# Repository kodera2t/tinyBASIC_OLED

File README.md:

# TinyBasicPlus_OLED_support
	! PLEASE select LCD version if you are searching character LCD support for TinyBasicPlus!!, If you need graphic LCD support for TinyBasicPluse, please select OLED version. !
	SSD1306 compatible OLED/LCD (128x64 dots) support is added to TinyBasicPlus, using Adafruit_GFX lib. 
	Frame buffer for 21x8 characters is added for text display. Along this support, TVout and PS2 keyboard support is subtracted, assuming re-programmed Xbox360 or serial console usage for input device. (you can add PS/2, if you need) I refered the source code by Ben Heck's Retro Basic Computer. GRAPHIC related BASIC commands (currently supporting only direct command):  CLS (clear screen), LINE x0,y0,x1,y1 CIRCLE x,y,radius FILLCIRCLE x,y,radius ROUNDRECT x,y,w,h,r FILLROUNDRECT x,y,w,h,r are added just for graphic test..
	Not only Arduino sketch, also circuit schematic and circuit pattern (.brd) is uploaded for your quick test of OLED version.

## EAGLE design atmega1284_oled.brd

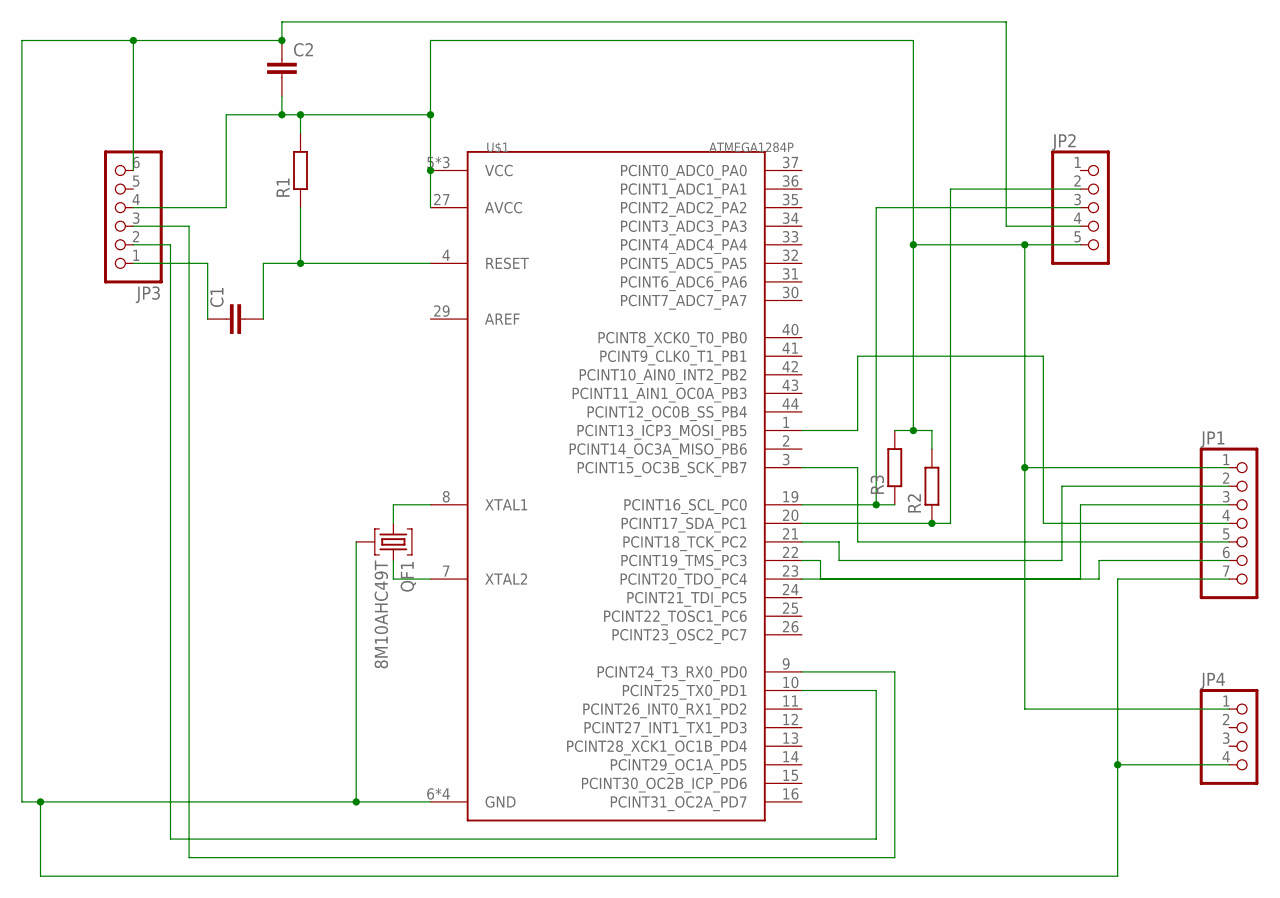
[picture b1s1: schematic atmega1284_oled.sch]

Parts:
C1, C2: C-EUC0805; C0805
JP1: PINHD-1X7; 1X07
JP2: PINHD-1X5; 1X05
JP3: PINHD-1X6; 1X06
JP4: PINHD-1X4; 1X04
QF1: 8M10AHC49T; HC49U
R1, R2, R3: R-EU_R0805; R0805
U$1: ATMEGA1284P; TQFP44

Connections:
unnamed: JP2.3, R3.1, U$1.19 (PCINT16_SCL_PC0)
unnamed: JP2.2, R2.1, U$1.20 (PCINT17_SDA_PC1)
unnamed: JP1.4, U$1.1 (PCINT13_ICP3_MOSI_PB5)
unnamed: C2.2, JP1.1, JP2.5, JP3.4, JP4.1, R1.2, R2.2, R3.2, U$1.5 (VCC), U$1.17 (VCC), U$1.27 (AVCC), U$1.38 (VCC)
unnamed: QF1.1, U$1.8 (XTAL1)
unnamed: QF1.3, U$1.7 (XTAL2)
unnamed: C2.1, JP1.7, JP2.4, JP3.6, JP4.4, QF1.2, U$1.6 (GND), U$1.18 (GND), U$1.28 (GND), U$1.39 (GND)
unnamed: JP1.5, U$1.3 (PCINT15_OC3B_SCK_PB7)
unnamed: JP1.2, U$1.21 (PCINT18_TCK_PC2)
unnamed: C1.2, R1.1, U$1.4 (RESET)
unnamed: C1.1, JP3.1
unnamed: JP3.2, U$1.10 (PCINT25_TX0_PD1)
unnamed: JP3.3, U$1.9 (PCINT24_T3_RX0_PD0)
unnamed: JP1.3, U$1.22 (PCINT19_TMS_PC3)
unnamed: JP1.6, U$1.23 (PCINT20_TDO_PC4)

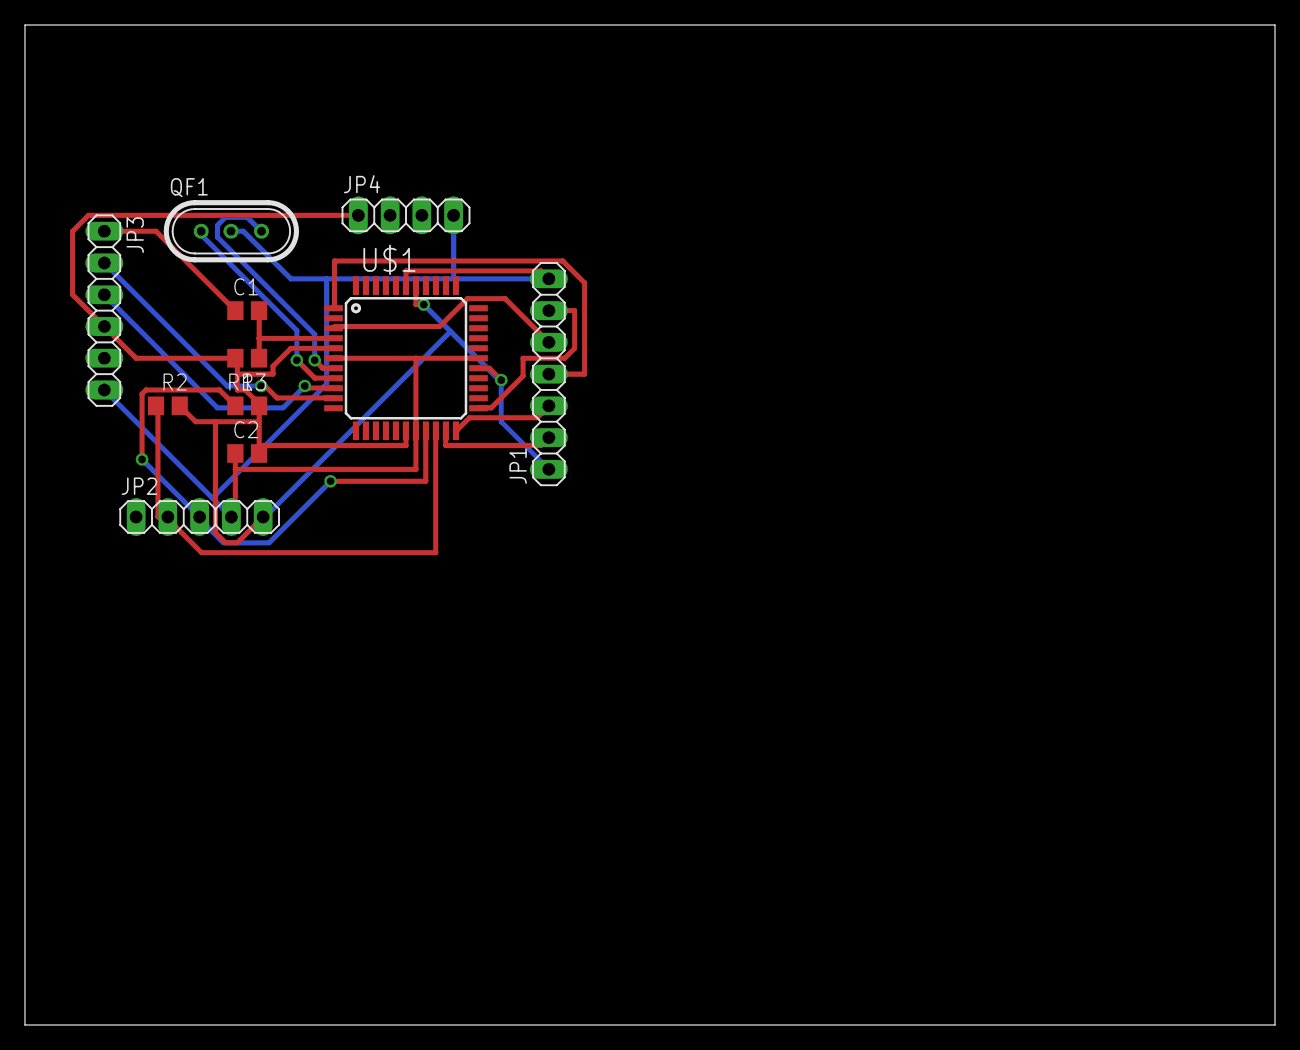
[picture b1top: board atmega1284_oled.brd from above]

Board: 2 copper layers, 100.0 x 80.0 mm, 11 parts (0 on the bottom side), 15 nets.

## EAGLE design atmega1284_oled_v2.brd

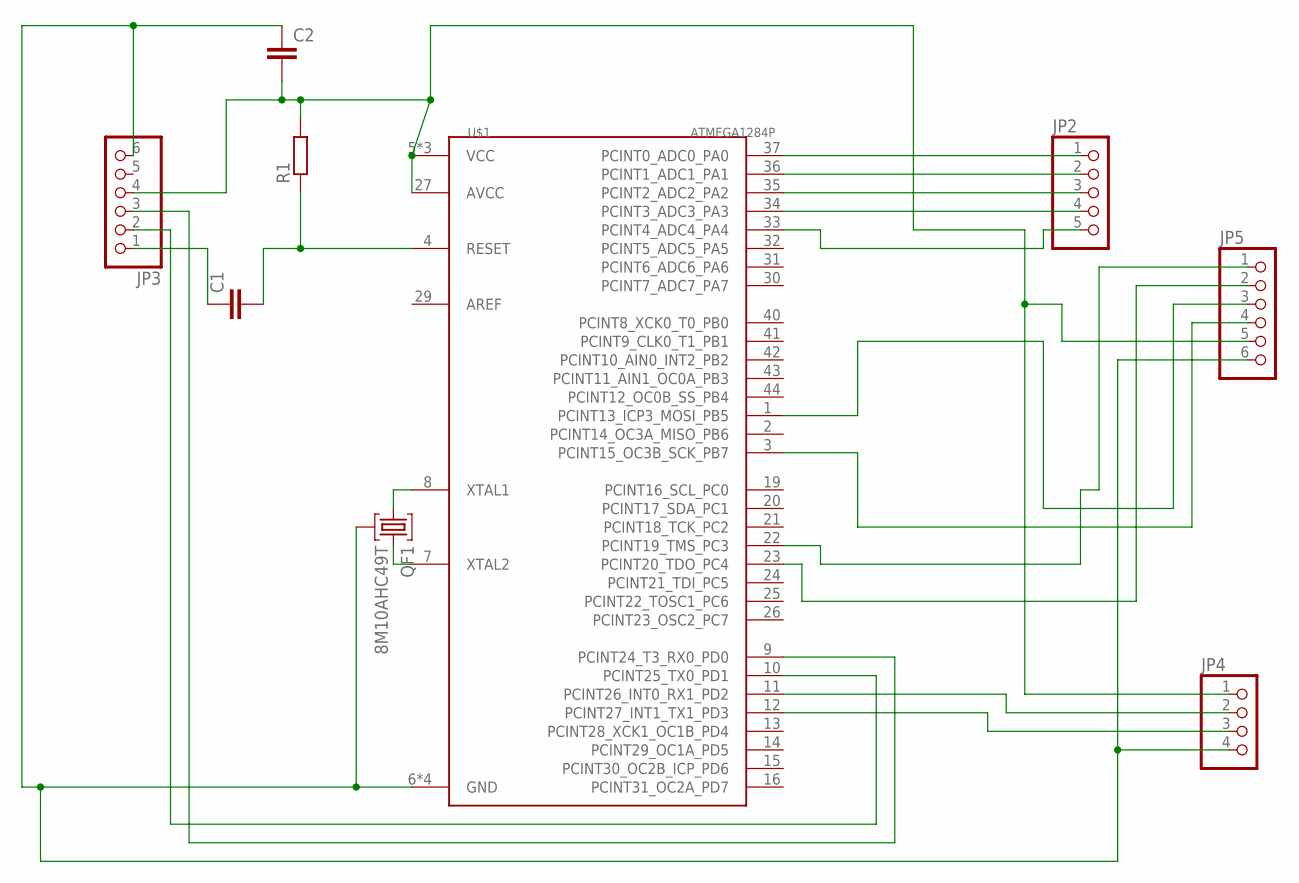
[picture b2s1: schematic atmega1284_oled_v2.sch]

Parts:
C1, C2: C-EUC0805; C0805
JP2: PINHD-1X5; 1X05
JP3, JP5: PINHD-1X6; 1X06
JP4: PINHD-1X4; 1X04
QF1: 8M10AHC49T; HC49U
R1: R-EU_R0805; R0805
U$1: ATMEGA1284P; TQFP44

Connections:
unnamed: JP2.1, U$1.37 (PCINT0_ADC0_PA0)
unnamed: JP2.2, U$1.36 (PCINT1_ADC1_PA1)
unnamed: JP5.3, U$1.1 (PCINT13_ICP3_MOSI_PB5)
unnamed: C2.2, JP3.4, JP4.1, JP5.5, R1.2, U$1.5 (VCC), U$1.17 (VCC), U$1.27 (AVCC), U$1.38 (VCC)
unnamed: QF1.1, U$1.8 (XTAL1)
unnamed: QF1.3, U$1.7 (XTAL2)
unnamed: C2.1, JP3.6, JP4.4, JP5.6, QF1.2, U$1.6 (GND), U$1.18 (GND), U$1.28 (GND), U$1.39 (GND)
unnamed: JP5.4, U$1.3 (PCINT15_OC3B_SCK_PB7)
unnamed: JP4.2, U$1.11 (PCINT26_INT0_RX1_PD2)
unnamed: C1.2, R1.1, U$1.4 (RESET)
unnamed: C1.1, JP3.1
unnamed: JP3.2, U$1.10 (PCINT25_TX0_PD1)
unnamed: JP3.3, U$1.9 (PCINT24_T3_RX0_PD0)
unnamed: JP5.1, U$1.22 (PCINT19_TMS_PC3)
unnamed: JP5.2, U$1.23 (PCINT20_TDO_PC4)
unnamed: JP4.3, U$1.12 (PCINT27_INT1_TX1_PD3)
unnamed: JP2.3, U$1.35 (PCINT2_ADC2_PA2)
unnamed: JP2.4, U$1.34 (PCINT3_ADC3_PA3)
unnamed: JP2.5, U$1.33 (PCINT4_ADC4_PA4)

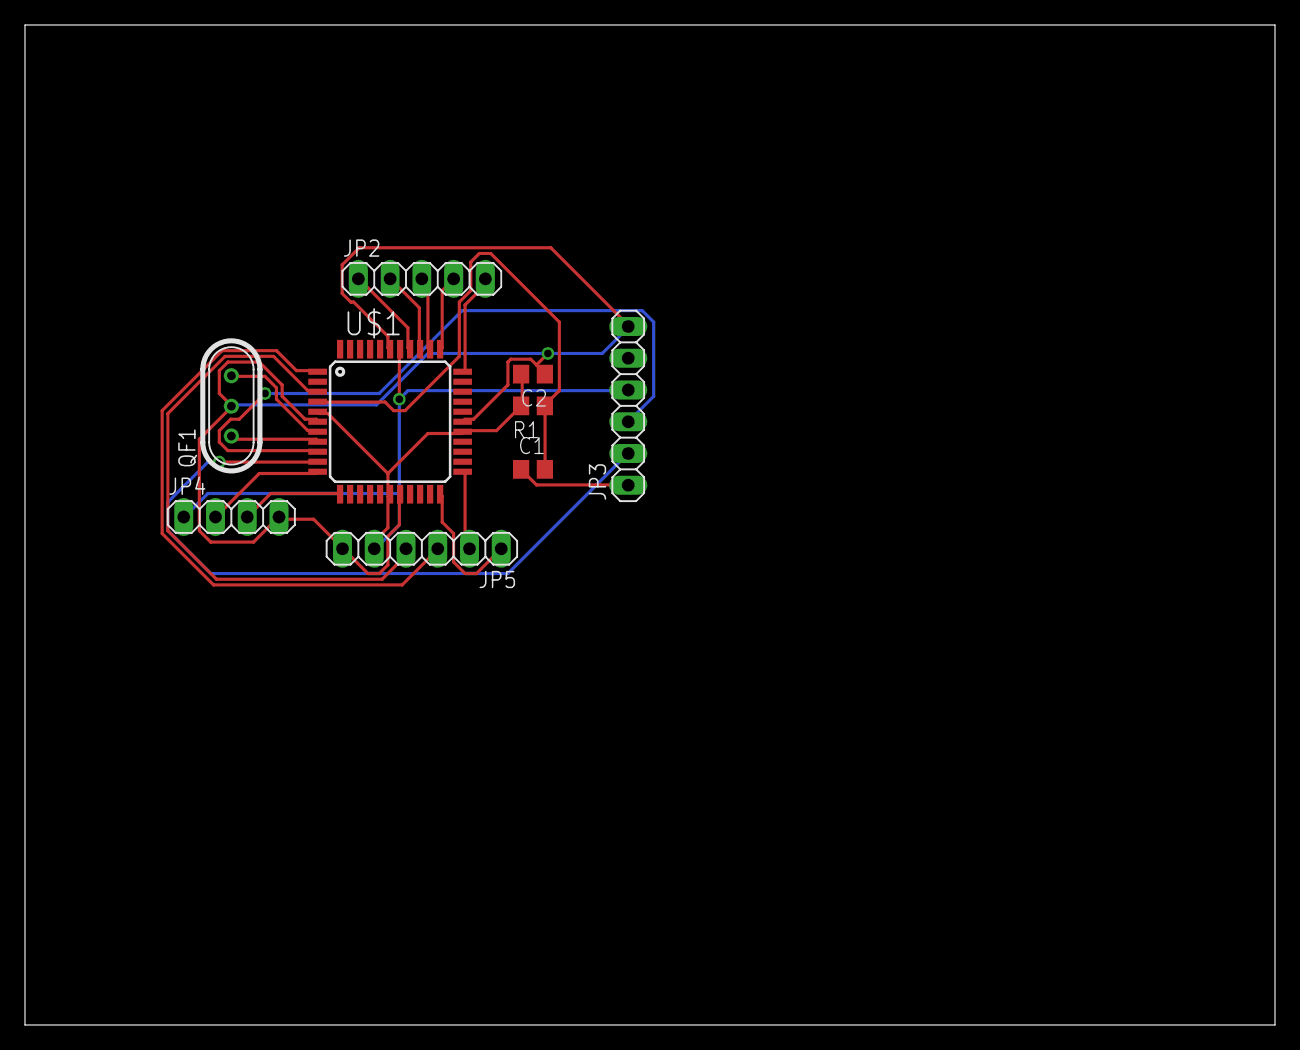
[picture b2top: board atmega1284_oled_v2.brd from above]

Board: 2 copper layers, 100.0 x 80.0 mm, 9 parts (0 on the bottom side), 19 nets.

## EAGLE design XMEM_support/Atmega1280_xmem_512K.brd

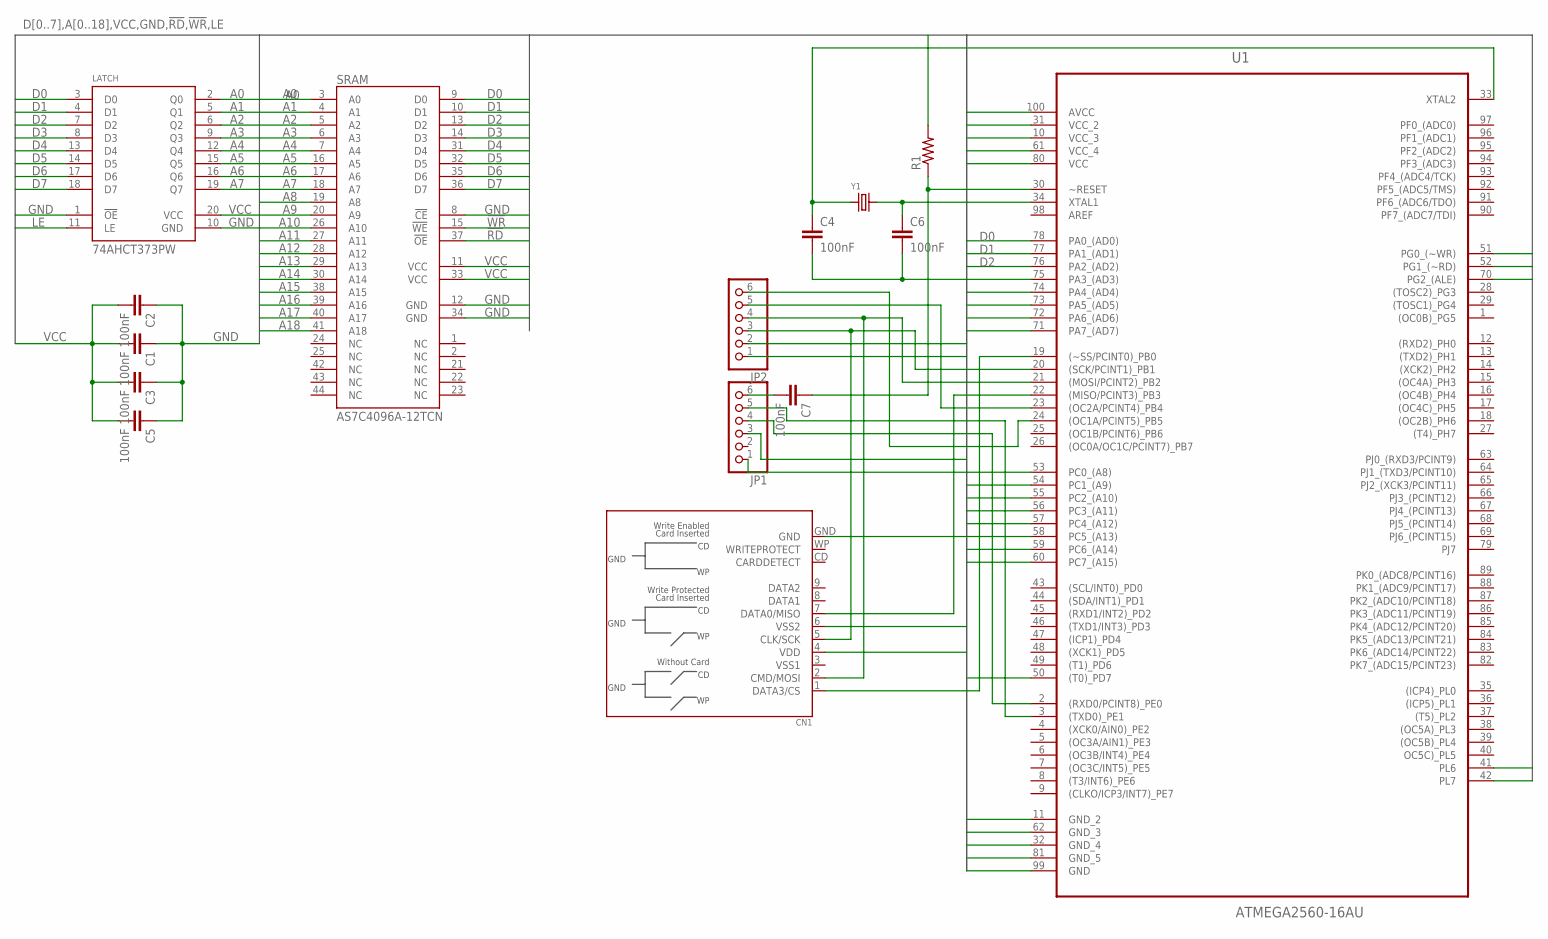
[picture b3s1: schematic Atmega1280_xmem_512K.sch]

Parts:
C1, C2, C3, C4, C5, C6, C7: 100nF; C0603
CN1: SDCARD; SDCARD_SMT_4U06132
JP1, JP2: HEADER-1X6; 1X06_OVAL
LATCH: 74AHCT373PW; TSSOP20
R1: R-US_R0603; R0603
SRAM: AS7C4096A-12TCN; TSOP44-II
U1: ATMEGA2560-16AU; QFP50P1600X1600X120-100N
Y1: CRYSTALSMD; HC49UP

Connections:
!RD: SRAM.37 (!OE), U1.52 (PG1_(~RD))
!WR: SRAM.15 (!WE), U1.51 (PG0_(~WR))
A0: LATCH.2 (Q0), SRAM.3 (A0)
A1: LATCH.5 (Q1), SRAM.4 (A1)
A2: LATCH.6 (Q2), SRAM.5 (A2)
A3: LATCH.9 (Q3), SRAM.6 (A3)
A4: LATCH.12 (Q4), SRAM.7 (A4)
A5: LATCH.15 (Q5), SRAM.16 (A5)
A6: LATCH.16 (Q6), SRAM.17 (A6)
A7: LATCH.19 (Q7), SRAM.18 (A7)
A8: SRAM.19 (A8), U1.53 (PC0_(A8))
A9: SRAM.20 (A9), U1.54 (PC1_(A9))
A10: SRAM.26 (A10), U1.55 (PC2_(A10))
A11: SRAM.27 (A11), U1.56 (PC3_(A11))
A12: SRAM.28 (A12), U1.57 (PC4_(A12))
A13: SRAM.29 (A13), U1.58 (PC5_(A13))
A14: SRAM.30 (A14), U1.59 (PC6_(A14))
A15: SRAM.38 (A15), U1.60 (PC7_(A15))
A16: SRAM.39 (A16), U1.50 ((T0)_PD7)
A17: SRAM.40 (A17), U1.42 (PL7)
A18: SRAM.41 (A18), U1.41 (PL6)
D0: LATCH.3 (D0), SRAM.9 (D0), U1.78 (PA0_(AD0))
D1: LATCH.4 (D1), SRAM.10 (D1), U1.77 (PA1_(AD1))
D2: LATCH.7 (D2), SRAM.13 (D2), U1.76 (PA2_(AD2))
D3: LATCH.8 (D3), SRAM.14 (D3), U1.75 (PA3_(AD3))
D4: LATCH.13 (D4), SRAM.31 (D4), U1.74 (PA4_(AD4))
D5: LATCH.14 (D5), SRAM.32 (D5), U1.73 (PA5_(AD5))
D6: LATCH.17 (D6), SRAM.35 (D6), U1.72 (PA6_(AD6))
D7: LATCH.18 (D7), SRAM.36 (D7), U1.71 (PA7_(AD7))
GND: C1.1, C2.1, C3.1, C4.2, C5.1, C6.2, CN1.6 (VSS2), CN1.GND, JP1.1, JP2.1, LATCH.1 (!OE), LATCH.10 (GND), SRAM.8 (!CE), SRAM.12 (GND), SRAM.34 (GND), U1.11 (GND_2), U1.32 (GND_4), U1.62 (GND_3), U1.81 (GND_5), U1.99 (GND)
LE: LATCH.11 (LE), U1.70 (PG2_(ALE))
unnamed: C6.1, U1.34 (XTAL1), Y1.2
unnamed: C4.1, U1.33 (XTAL2), Y1.1
unnamed: C7.1, R1.1, U1.30 (~RESET)
unnamed: C7.2, JP1.6
unnamed: JP1.5, U1.3 ((TXD0)_PE1)
unnamed: JP1.4, U1.2 ((RXD0/PCINT8)_PE0)
unnamed: CN1.5 (CLK/SCK), JP2.3, U1.20 ((SCK/PCINT1)_PB1)
unnamed: CN1.2 (CMD/MOSI), JP2.4, U1.21 ((MOSI/PCINT2)_PB2)
unnamed: JP2.5, U1.23 ((OC2A/PCINT4)_PB4)
unnamed: JP2.6, U1.24 ((OC1A/PCINT5)_PB5)
unnamed: CN1.7 (DATA0/MISO), U1.22 ((MISO/PCINT3)_PB3)
unnamed: CN1.1 (DATA3/CS), U1.19 ((~SS/PCINT0)_PB0)
VCC: C1.2, C2.2, C3.2, C5.2, CN1.4 (VDD), JP1.3, JP2.2, LATCH.20 (VCC), R1.2, SRAM.11 (VCC), SRAM.33 (VCC), U1.10 (VCC_3), U1.31 (VCC_2), U1.61 (VCC_4), U1.80 (VCC), U1.100 (AVCC)

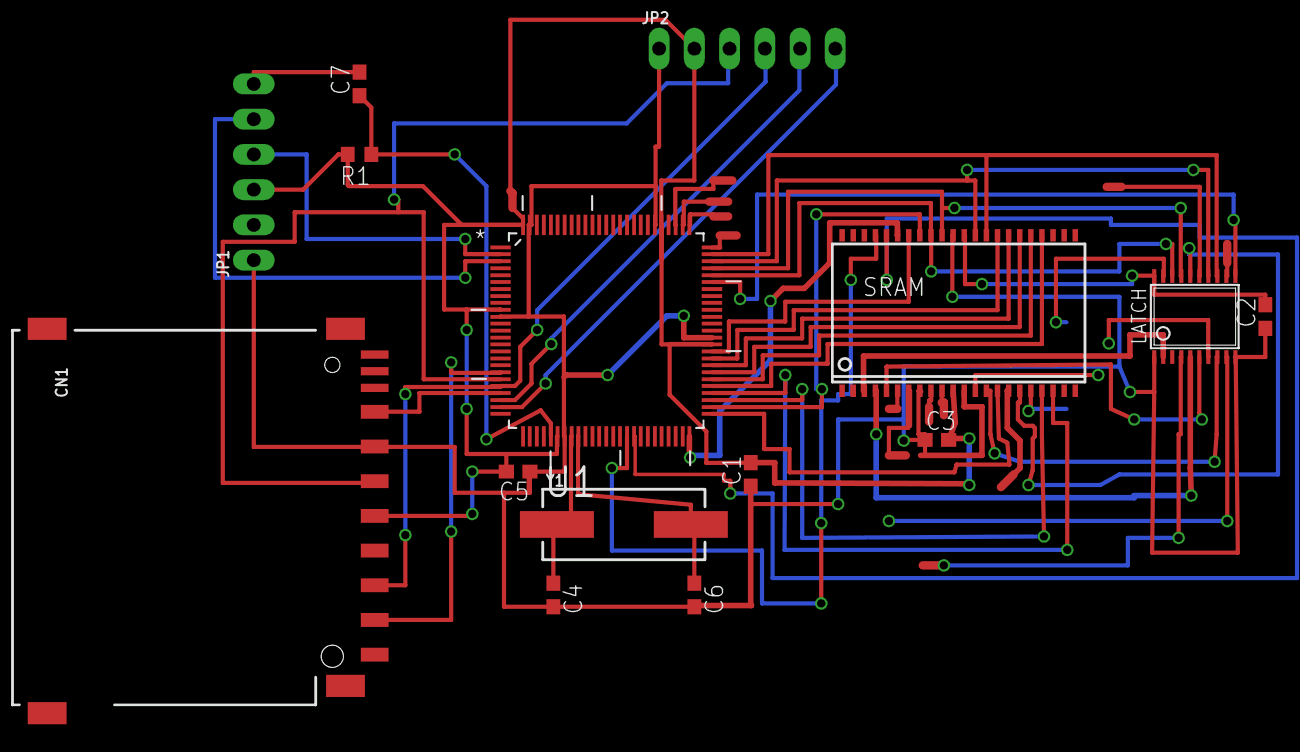
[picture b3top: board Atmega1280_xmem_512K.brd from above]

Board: 2 copper layers, 15 parts (0 on the bottom side), 44 nets.

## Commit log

2017-05-06 initial submission

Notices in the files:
parts and their libraries:
OLED_mod: This work is placed in the public domain, and may be freely used for commercial and non-commercial work with the following conditions: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
